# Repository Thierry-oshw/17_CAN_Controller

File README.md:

# Can controller and CAN transceiver module

Can module to easily add CAN support to anything with SPI

[Link for controller](https://github.com/Thierry-oshw/17_CAN_Controller)

[Link for transceiver](https://github.com/Thierry-oshw/15_XCAN)

## Features
- Small (Controller is 18x20 mm, Transceiver is 17x15 mm)
- Cheap (2 layer and components on one side)
- 2.54 header + castellated pad for direct board to board soldering

## Made with

- [Kicad V6](https://www.kicad.org/)

## Schematic

### 15 XCAN Schematic

### 17 CAN Controller Schematic

## Build the PCB

PCB has been fully tested on multiple projects

[CAN Controller build files](https://github.com/Thierry-oshw/17_CAN_Controller/tree/main/fabrication_2023_04_23)

[CAN Transceiver build files without castellated holes](https://github.com/Thierry-oshw/15_XCAN/tree/main/fabrication_2023_04_21)

[CAN Transceiver build files with castellated holes](https://github.com/Thierry-oshw/15_XCAN/tree/main/fabrication_2023_04_21_CH)

## Authors

- Thierry Orlandi ([Hardware Freelance](https://www.linkedin.com/in/thierry-orlandi))
- Yohann Belair ([R&D Freelance](https://github.com/ciborg971))

## License
[CERN Open Hardware Licence Version 2](https://github.com/Thierry-oshw/17_CAN_Controller/blob/main/LICENSE.txt)

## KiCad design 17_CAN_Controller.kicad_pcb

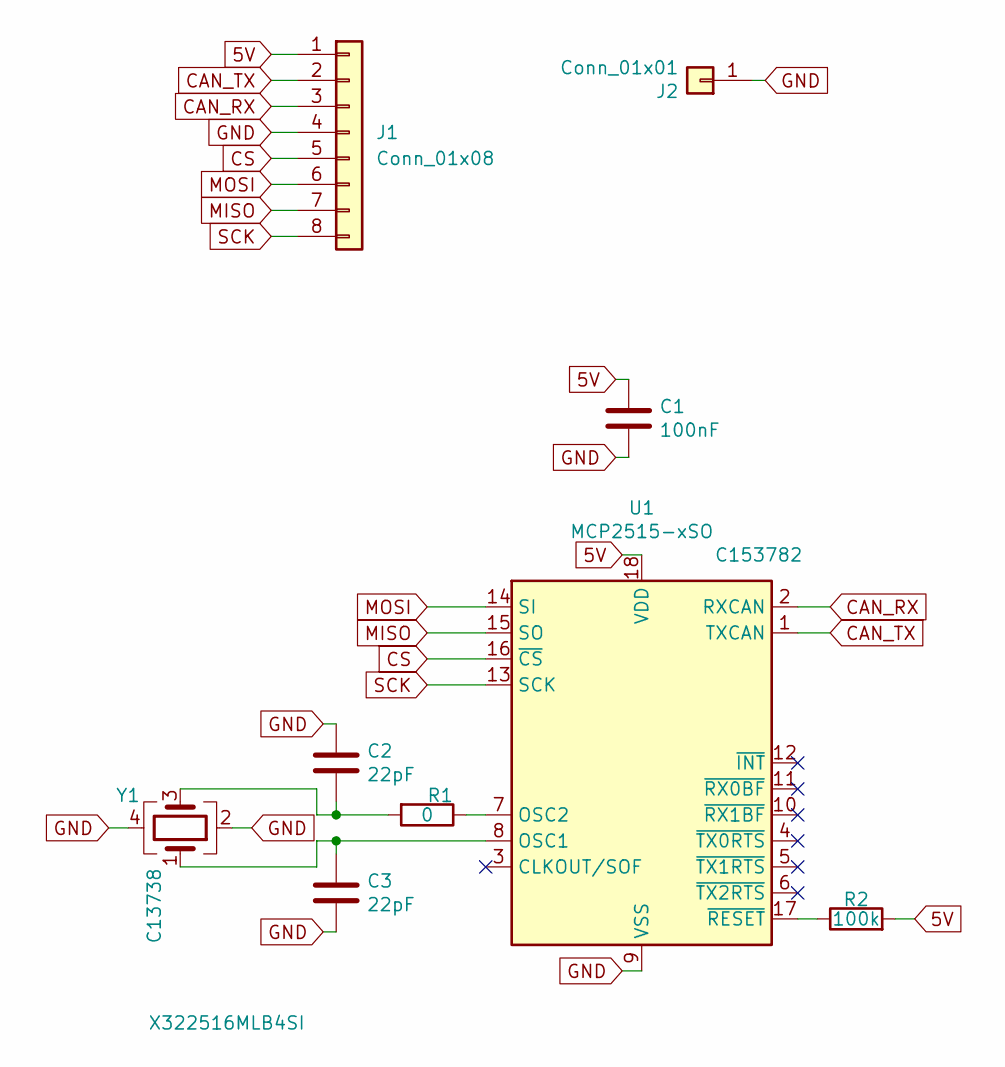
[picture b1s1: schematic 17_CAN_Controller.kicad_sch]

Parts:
C1: 100nF; C_0603_1608Metric; LCSC C14663
C2, C3: 22pF; C_0603_1608Metric; LCSC C1653
J1: Conn_01x08; PinHeader_1x08_P2.54mm_Vertical
J2: Conn_01x01; PinHeader_1x01_P2.54mm_Vertical
R1: 0; R_0603_1608Metric; LCSC C21189
R2: 100k; R_0603_1608Metric; LCSC C25803
U1: MCP2515-xSO; SOIC-18W_7.5x11.6mm_P1.27mm; LCSC C153782
Y1: X322516MLB4SI; Crystal_SMD_3225-4Pin_3.2x2.5mm; LCSC C13738

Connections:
5V: C1.1, J1.1, R2.2, U1.18 (VDD)
CAN_RX: J1.3, U1.2 (RXCAN)
CAN_TX: J1.2, U1.1 (TXCAN)
CS: J1.5, U1.16 (~CS)
GND: C1.2, C2.1, C3.2, J1.4, J2.1, U1.9 (VSS), Y1.2, Y1.4
MISO: J1.7, U1.15 (SO)
MOSI: J1.6, U1.14 (SI)
unnamed: C3.1, U1.8 (OSC1), Y1.1
unnamed: R1.1, U1.7 (OSC2)
unnamed: C2.2, R1.2, Y1.3
unnamed: R2.1, U1.17 (~RESET)
SCK: J1.8, U1.13 (SCK)

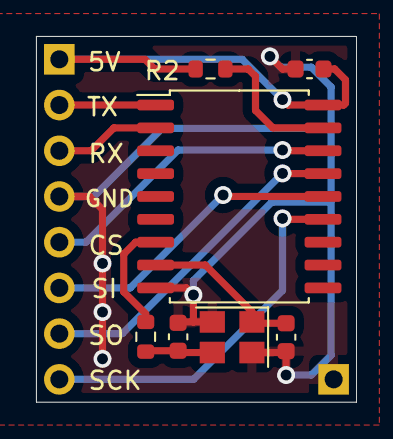
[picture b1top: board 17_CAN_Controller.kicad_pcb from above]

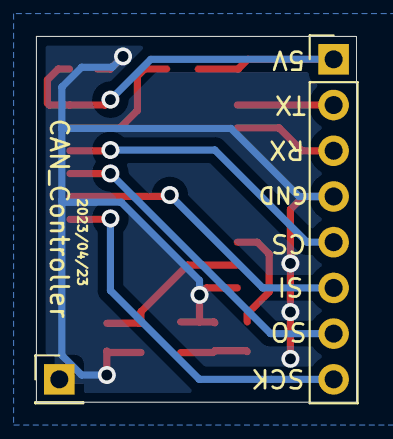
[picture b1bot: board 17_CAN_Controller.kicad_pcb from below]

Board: 2 copper layers, 17.8 x 20.3 mm, 9 parts (2 on the bottom side), 12 nets.

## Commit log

2021-06-01 schema + routage
2021-07-26 maj split librairies
2022-10-31 maj kicad 6
    + correction chemin
    + step
2022-11-03 maj réduction de taille
2022-11-03 connecteur passe de wrl à step
2022-11-06 gerbers maj kicad 6 jlcpcb
2022-11-06 maj kicad 6 jlcpcb
2022-11-07 zip pour voir position et bom
2023-04-23 maj librairies et silk
2023-05-02 chgt nom fichier licence
2023-05-28 maj readme
